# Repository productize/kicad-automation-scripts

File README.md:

KiCad automation scripts
========================

A bunch of scripts to automate [KiCad] processes using a combination of the
PCBNew Python library and UI automation with [xdotool].

This work is based in big parts on Scott Bezek's scripts in his
[split-flap display project][split-flap].
For more info see his [excellent blog posts][scot's blog].

Currently tested and working:

- Exporting schematics to PDF and SVG
- Exporting layouts to PDF and SVG
- Running ERC on schematics
- Running DRC on layouts

## Versions

This repository has a branch per supported major KiCad version, prefixed with
`kicad-`. Note that installation instructions and supported features can be
different per version.

The master branch and latest Docker tag will always be the latest supported
stable KiCad version.

## Installation

### Using Docker

Build and run the docker image:

```
docker build -t kicad-automation-scripts .
docker run --rm -it -v <path to a kicad project>:/kicad-project kicad-automation-scripts
```

Or fetch it from [Dockerhub]:

```
docker run --rm -it -v <path to a kicad project>:/kicad-project productize/kicad-automation-scripts
```

### Installation on your own machine:

If you want to use these scripts directly on your system, you should be able to
get it to work by installing the folowing dependencies:

This tool has the following dependencies:
- KiCad
- python
- python-pip
- xvfb
- recordmydesktop
- xdotool
- xclip

The Python dependencies (excluding KiCad) are listed in
[eeschema/requirements.txt][eeschema/requirements.txt] and can be installed with

```
pip install -r eeschema/requirements.txt
```

### Installation on Ubuntu/Debian:

```
sudo apt-get install -y kicad python python-pip xvfb recordmydesktop xdotool xclip
```

## Usage

In the Docker image or on a system with all required dependencies installed you
can use the following commands:

### Run schematic ERC:

```
python -m kicad-automation.eeschema.schematic run_erc /kicad-project/<some-schematic>.sch <build_dir>
```

Add the flag `--warnings_as_errors` to make all warnings also return an error code of `1`.

### Export a schematic to PDF or SVG

```
python -m kicad-automation.eeschema.schematic export /kicad-project/<some-schematic>.sch <build_dir> <svg or pdf> <all-pages (True or False)>
```

### Run layout DRC:

```
python -m kicad-automation.pcbnew_automation.run_drc /kicad-project/<some-layout>.kicad_pcb <build_dir>
```

### Generate a zip file with gerber files for PCB manufacuring:

```
python -m kicad-automation.pcbnew_automation.plot /kicad-project/<some-layout>.kicad_pcb <plot_dir> [<layers to plot>]
```

### Generate a pdf with the layout layers and drill map file:

```
python -m kicad-automation.pcbnew_automation.plot -f pdf /kicad-project/<some-layout>.kicad_pcb <plot_dir> [<layers to plot>]
```

## Hacking

If you want to test the scripts in this repository and run them inside a docker
image, the base image can be used. This base image contains all the required
dependencies and the required environment for the script to work.

To build and run the base image:

```
docker build -f Dockerfile-base -t kicad-automation-base .
docker run --rm -it -v <path to a kicad project>/kicad-project  -v `pwd`/src:/usr/lib/python2.7/dist-packages/kicad-automation kicad-automation-base
```

Or fetch it from [Dockerhub]:

```
docker run --rm -it -v <path to a kicad project>:/kicad-project -v `pwd`/src:/usr/lib/python2.7/dist-packages/kicad-automation productize/kicad-automation-base
```

The scripts can now be used the same way as in the main image, but changes
on the host will automatically be reflected on the container (though note
that Python does not autoreload libraries).

[KiCad]: http://kicad.org/
[xdotool]: https://github.com/jordansissel/xdotool
[split-flap]: https://github.com/scottbez1/splitflap
[scot's blog]: https://scottbezek.blogspot.be/2016/04/scripting-kicad-pcbnew-exports.html
[Dockerhub]: https://hub.docker.com/r/productize/kicad-automation-scripts

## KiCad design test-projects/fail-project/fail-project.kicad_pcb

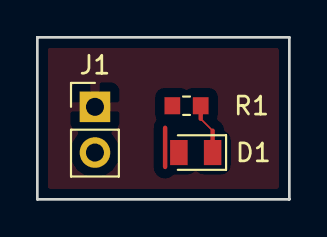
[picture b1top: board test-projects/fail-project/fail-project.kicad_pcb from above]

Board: 2 copper layers, 14.0 x 9.0 mm, 3 parts (0 on the bottom side), 2 nets.

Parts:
D1: LED; LED_0805_2012Metric
J1: Conn_01x02; PinHeader_1x02_P2.54mm_Vertical
R1: 330; R_0603_1608Metric

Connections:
unnamed: D1.1, R1.1
VCC: D1.2, J1.2

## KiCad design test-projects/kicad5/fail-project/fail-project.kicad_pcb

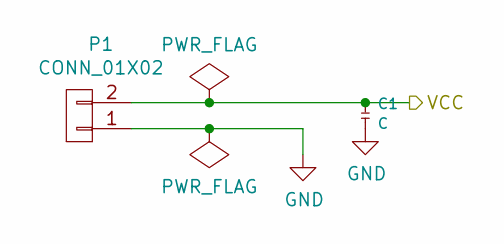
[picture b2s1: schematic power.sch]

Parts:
C1: C; C_0402_1005Metric
P1: CONN_01X02; JST_JWPF_B02B-JWPF-SK-R_1x02_P2.00mm_Vertical

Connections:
/Power/VCC: C1.1, P1.2; also elsewhere on the board
GND: C1.2, P1.1; also elsewhere on the board

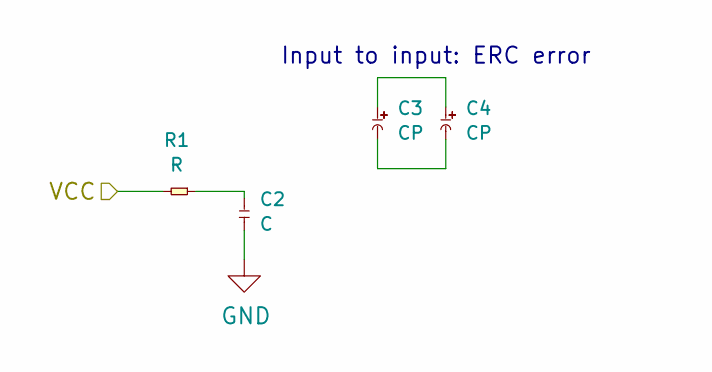
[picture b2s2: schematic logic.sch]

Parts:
C2: C; C_0402_1005Metric
C3, C4: CP; CP_Elec_3x5.3
R1: R; R_0402_1005Metric

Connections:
/Power/VCC: R1.1; also elsewhere on the board
GND: C2.2; also elsewhere on the board
unnamed: C2.1, R1.2
unnamed: C3.1, C4.1
unnamed: C3.2, C4.2

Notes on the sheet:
Input to input: ERC error

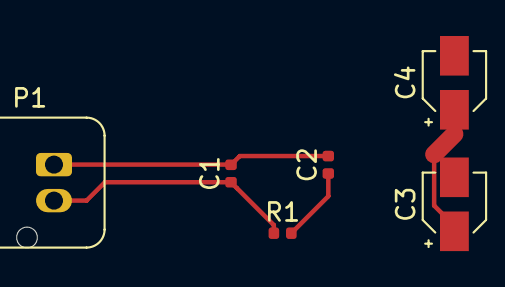
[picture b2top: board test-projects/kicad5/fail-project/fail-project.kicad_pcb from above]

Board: 2 copper layers, 6 parts (0 on the bottom side), 5 nets.

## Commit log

2018-04-06 Make README more accessible for beginners
2018-04-06 eeschema: Ignore missing libraries
2018-04-06 eeschema: Explicitly focus the library warning window, add log message
2018-04-06 Add dockerfile
2018-04-06 Inherit Docker image from productize/kicad
2018-05-06 Make it useable as Python module
2018-06-01 Fix export_util import
2018-06-01 Make export_util work in library again
2018-06-01 Add SVG export option
2018-07-06 Remove rev_info, make format option case-insensitive and make SVG default format
2018-07-06 Add some mising pcbnew processing scripts
2018-07-06 Make exporting all pages in schematic optional
2018-07-06 make sure plot always starts from same option
2018-08-03 Remove git dependend code from layout render sripts and make it accept the file as argument
2018-08-03 Use python3 and clean up apt cache files
2018-08-03 Remove unused files and add .dockerignore
2018-08-16 Make pcbnew usefull as lib
2018-08-16 Add __init__.pu to util
2018-08-16 Revert back to Python2, clean up docker image and add scripts to python dist-packages
2018-08-16 Clean up export schematic
2018-09-07 Fix git ignore not ignoring pyc in root
2018-09-07 Get layer names and colors using pcbnew lib
2019-04-02 Add command to run ERC on KiCad schematics
2019-04-03 Add UI automation for PCBNew DRC
2019-04-04 Optimize wait_for_window to automaticaly focus the windows
    This pretty much halves the amount of calls to xdotool, since we
    almost always want to focus the window after waiting for it.
    The functionality can still be disabled by passing focus=False to
    wait_for_window.
2019-04-04 Make DRC work on KiCad 5.0.1
2019-04-05 Minimize calls to xdotool, use clipboard and file waiting when plotting
2019-04-05 Add kicad 5 test projects
2019-04-05 Add default config and empty lib tables
2019-04-05 Fix some mistakes in README
2019-04-05 Check for schematic to exist before attempting to open it
2019-04-05 Add gitlab CI config
2019-04-05 Fix script location in CI
2019-04-05 Add artifacts
2019-04-05 Handle schematic being created by newer versions of eeschema
2019-04-05 Woops, forgot to ignore newer version when plotting
2019-04-05 Use different docker image built localy
2019-04-23 Look for correct project rescue window and correct ERC menu
    At some pint it seems like the ERC menu was reset to the kiCad 4
    method...
2019-04-23 Revert "Use different docker image built localy"
    This reverts commit d708e0f639932279bae95bfb8f84e24bc1a293c9.
2019-04-23 Add gitlab CI config for kicad 4
2019-04-23 Update test projects to KiCad 5
2019-04-23 Allow use of relative path to schematic
2019-04-23 Fix not checking for open files correctly
2019-04-23 Make schematic export work with KiCad 5
2019-04-23 Update test project and use scripts in repo in CI
2019-04-23 Add artifacts to schematic export
2019-04-23 Fix running DRC on KiCAD 5
    - Moving the mouse seems to rebuild (initialy build) the menu.
    - Some UI changes where made to the DRC modal window
2019-04-23 Add running DRC to gitlab ci
2019-04-23 Resize window to trigger menu build
    It looks like moving the mouse doesn't always work
2019-04-23 Uptimize calls to xdotool when running DRC
2019-04-23 Fix exporting SVG of a layout
2019-04-23 Add exporting layout SVG to gitlab CI
2019-04-26 Testing manual release
2019-04-26 Attempt to get variables working
2019-04-26 Test creating a release
2019-04-26 fix release script
2019-04-26 Sich, YAML sucks
2019-04-26 Enable CI trace for release job
2019-04-26 Fix variables indentation
2019-04-26 Another attempt at fixing release job
2019-05-07 Build docker image on gitlab
    This way we don't have to wait for Docker hub and we can always be
    sure the tests are run on the correct base image.
2019-05-07 Pass the docker tag for the base image
2019-05-07 Pass docker password over stdin iof as arg
    This removes a warning message.
2019-05-09 Made layout export to zipped gerbers and pdf working
2019-05-09 Remove accidentally added WiP code breaking CI
2019-05-09 Move util in src folder
2019-05-09 Remove temp dir when done plotting
2019-05-09 Fix plotting gerber not checking if drill file exists
2019-05-09 Add Apache LICENSE file
2019-05-19 Export junit-xml for schematic ERC, partly implements #2
2019-05-19 Fix outdated runner?
2019-05-19 Well, I guess I should use my own runner then...
2019-05-19 Treat warnings as errors
2019-05-20 Add test suite for last (potentially only) sheet
2019-07-18 Disable junit-xml generation in CI
2019-08-05 Minor typo fixes.
2020-03-12 Bump psutil from 5.6.1 to 5.6.6 in /src
    Bumps [psutil](https://github.com/giampaolo/psutil) from 5.6.1 to 5.6.6.
    - [Release notes](https://github.com/giampaolo/psutil/releases)
    - [Changelog](https://github.com/giampaolo/psutil/blob/master/HISTORY.rst)
    - [Commits](https://github.com/giampaolo/psutil/compare/release-5.6.1...release-5.6.6)
2021-02-11 Fixed run_erc documentation in README. Added little tibit on --warnings_as_errors to README.
2021-05-23 Update README.md
    Fixed the path for installing the requirements
2021-09-10 Implement Specctra DSN export
2021-09-10 Implement Specctra SES import
2021-09-10 Fix typo
2021-11-08 Update README.md
    https://forum.kicad.info/t/warning-avoid-all-links-to-kicad-pcb-org-use-kicad-org/31521
2022-04-22 Bump pypdf2 from 1.26.0 to 1.27.5 in /src
    Bumps [pypdf2](https://github.com/py-pdf/PyPDF2) from 1.26.0 to 1.27.5.
    - [Release notes](https://github.com/py-pdf/PyPDF2/releases)
    - [Changelog](https://github.com/py-pdf/PyPDF2/blob/main/CHANGELOG)
    - [Commits](https://github.com/py-pdf/PyPDF2/compare/1.26.0...1.27.5)
    ---
    updated-dependencies:
